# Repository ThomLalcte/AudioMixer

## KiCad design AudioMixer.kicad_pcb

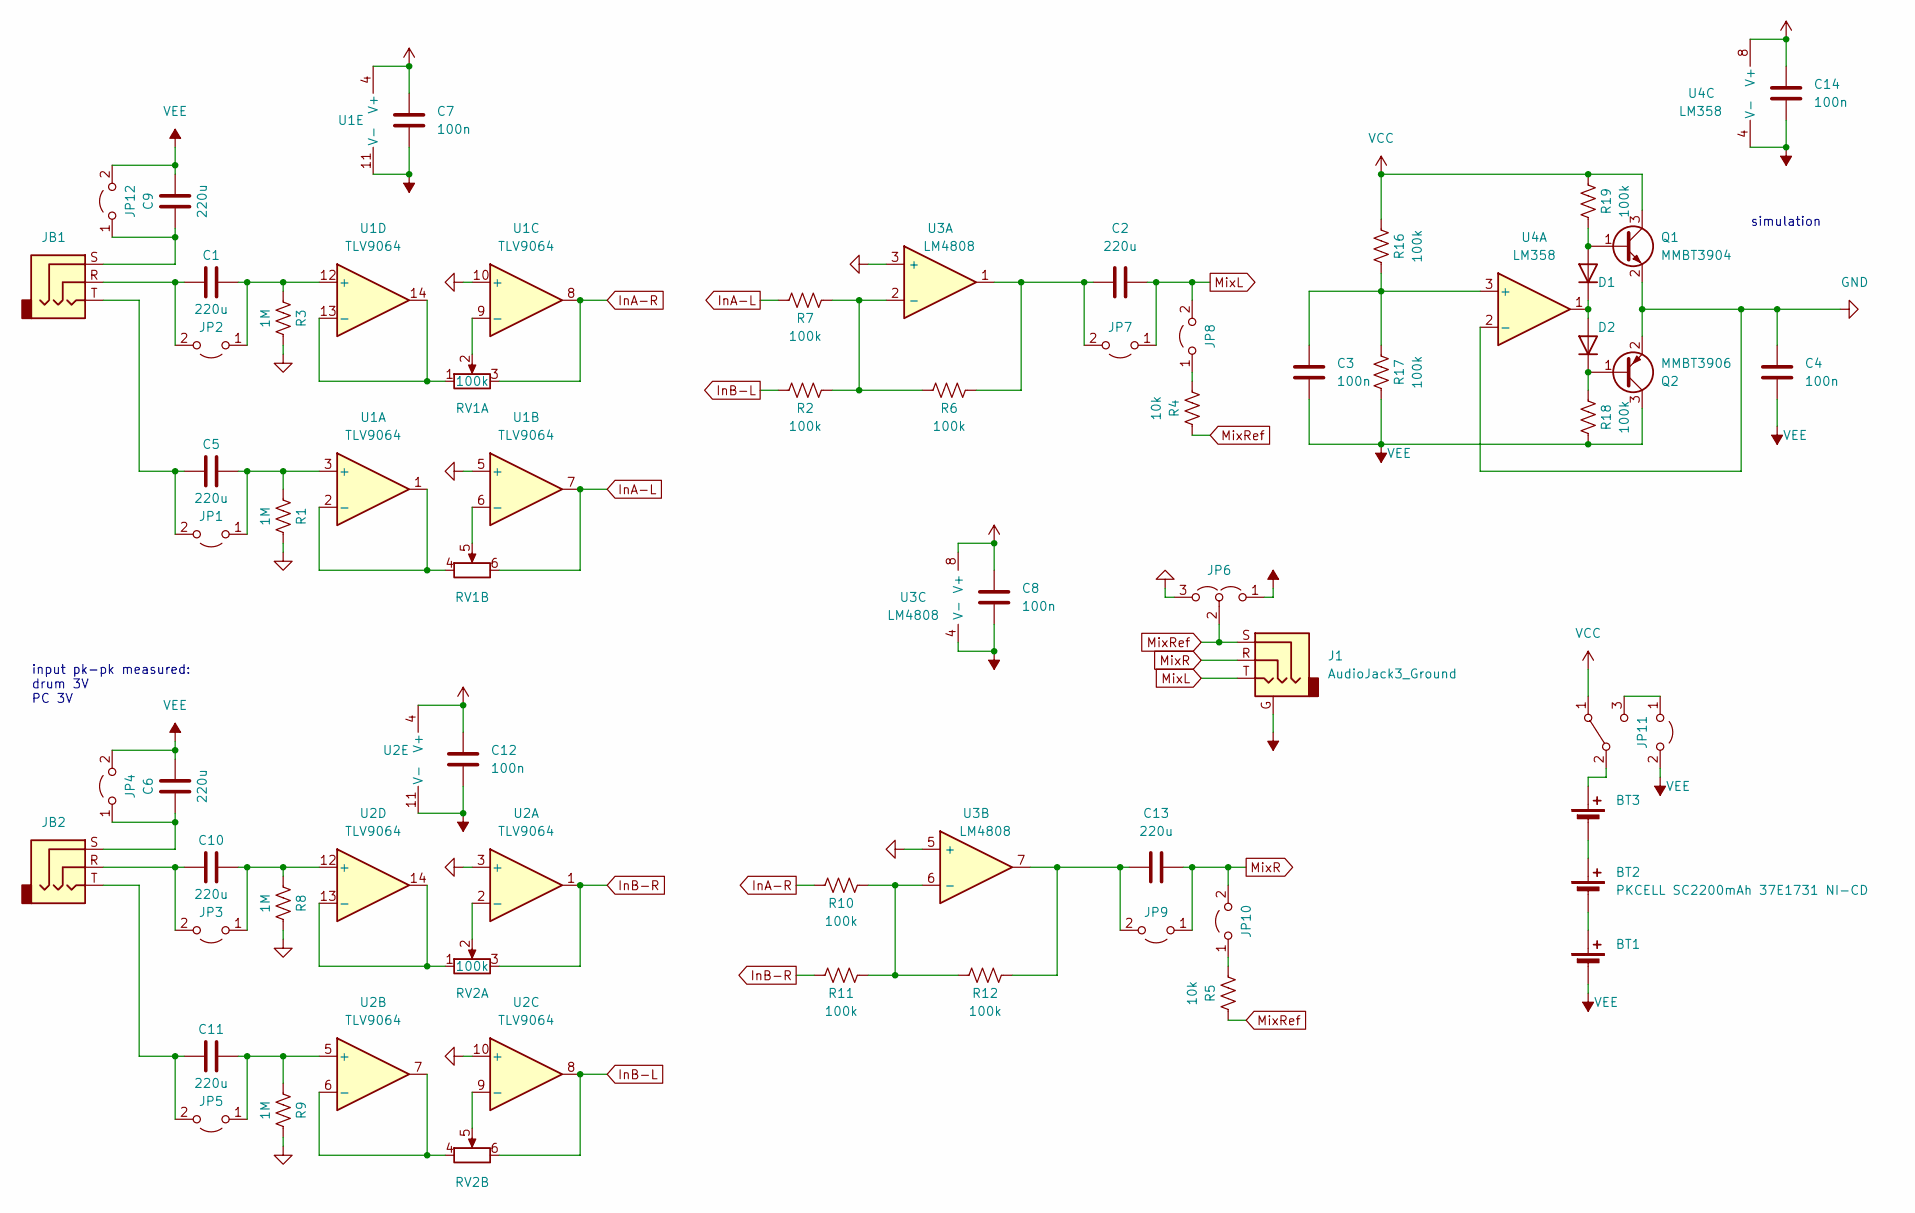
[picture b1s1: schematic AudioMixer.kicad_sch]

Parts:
BT1, BT2, BT3: PKCELL SC2200mAh 37E1731 NI-CD; Ni-Cd
C1, C2, C5, C6, C9, C10, C11, C13: 220u; CP_Radial_D5.0mm_P2.00mm
C3, C4, C7, C8, C12, C14: 100n; C_0603_1608Metric_Pad1.08x0.95mm_HandSolder
D1, D2: 1N4148; D_SOD-123
J1: AudioJack3_Ground; Jack_3.5mm_CUI_SJ-3524-SMT_Horizontal
JB1, JB2: AudioJack3; C18594
JP1, JP2, JP3, JP4, JP5, JP7, JP8, JP9, JP10, JP11, JP12: Jumper_2_Open; PinHeader_1x02_P2.54mm_Vertical
JP6: Jumper_3_Open; PinHeader_1x03_P2.54mm_Vertical
Q1: MMBT3904; SOT-23
Q2: MMBT3906; SOT-23
R1, R3, R8, R9: 1M; R_0805_2012Metric_Pad1.20x1.40mm_HandSolder
R2, R6, R7, R10, R11, R12, R16, R17, R18, R19: 100k; R_0805_2012Metric_Pad1.20x1.40mm_HandSolder
R4, R5: 10k; R_0805_2012Metric_Pad1.20x1.40mm_HandSolder
RV1, RV2: 100k; Potentiometer_Bourns_PTA3044_Double_Slide
SW1: SW_SPDT; C128955
U1, U2: TLV9064; TSSOP-14_4.4x5mm_P0.65mm
U3: LM4808; SOIC-8_3.9x4.9mm_P1.27mm
U4: LM358; SOIC-8_3.9x4.9mm_P1.27mm

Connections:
GND: C4.1, JP6.3 (B), Q1.2 (E), Q2.2 (E), R1.1, R3.1, R8.1, R9.1, U1.5 (+), U1.10 (+), U2.3 (+), U2.10 (+), U3.3 (+), U3.5 (+), U4.2 (-)
InA-L: R7.1, RV1.6, U1.7
InA-R: R10.1, RV1.3, U1.8
InB-L: R2.1, RV2.6, U2.8
InB-R: R11.1, RV2.3, U2.1
MixL: C2.2, J1.T, JP7.1 (A), JP8.2 (B)
MixR: C13.2, J1.R, JP9.1 (A), JP10.2 (B)
MixRef: J1.S, JP6.2 (C), R4.2, R5.2
unnamed: BT1.1 (+), BT2.2 (-)
unnamed: BT2.1 (+), BT3.2 (-)
unnamed: BT3.1 (+), SW1.2 (B)
unnamed: D1.2 (A), Q1.1 (B), R19.1
unnamed: D1.1 (K), D2.2 (A), U4.1
unnamed: D2.1 (K), Q2.1 (B), R18.2
unnamed: C5.1, JP1.1 (A), R1.2, U1.3 (+)
unnamed: C5.2, JB1.T, JP1.2 (B)
unnamed: C1.1, JP2.1 (A), R3.2, U1.12 (+)
unnamed: C1.2, JB1.R, JP2.2 (B)
unnamed: C10.1, JP3.1 (A), R8.2, U2.12 (+)
unnamed: C10.2, JB2.R, JP3.2 (B)
unnamed: C6.2, JB2.S, JP4.1 (A)
unnamed: C11.1, JP5.1 (A), R9.2, U2.5 (+)
unnamed: C11.2, JB2.T, JP5.2 (B)
unnamed: C2.1, JP7.2 (B), R6.2, U3.1
unnamed: JP8.1 (A), R4.1
unnamed: C13.1, JP9.2 (B), R12.2, U3.7
unnamed: JP10.1 (A), R5.1
unnamed: JP11.1 (A), SW1.3 (C)
unnamed: C9.2, JB1.S, JP12.1 (A)
unnamed: RV1.4, U1.1, U1.2 (-)
unnamed: RV1.5, U1.6 (-)
unnamed: RV1.2, U1.9 (-)
unnamed: RV1.1, U1.13 (-), U1.14
unnamed: RV2.2, U2.2 (-)
unnamed: RV2.4, U2.6 (-), U2.7
unnamed: RV2.5, U2.9 (-)
unnamed: RV2.1, U2.13 (-), U2.14
unnamed: R2.2, R6.1, R7.2, U3.2 (-)
unnamed: R10.2, R11.2, R12.1, U3.6 (-)
unnamed: C3.1, R16.1, R17.2, U4.3 (+)
VCC: C7.2, C8.2, C12.2, C14.2, Q1.3 (C), R16.2, R19.2, SW1.1 (A), U1.4 (V+), U2.4 (V+), U3.8 (V+), U4.8 (V+)
VEE: BT1.2 (-), C3.2, C4.2, C6.1, C7.1, C8.1, C9.1, C12.1, C14.1, J1.G, J1.TN, JP4.2 (B), JP6.1 (A), JP11.2 (B), JP12.2 (B), Q2.3 (C), R17.1, R18.1, U1.11 (V-), U2.11 (V-), U3.4 (V-), U4.4 (V-)

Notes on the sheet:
simulation
input pk-pk measured: drum 3V PC 3V

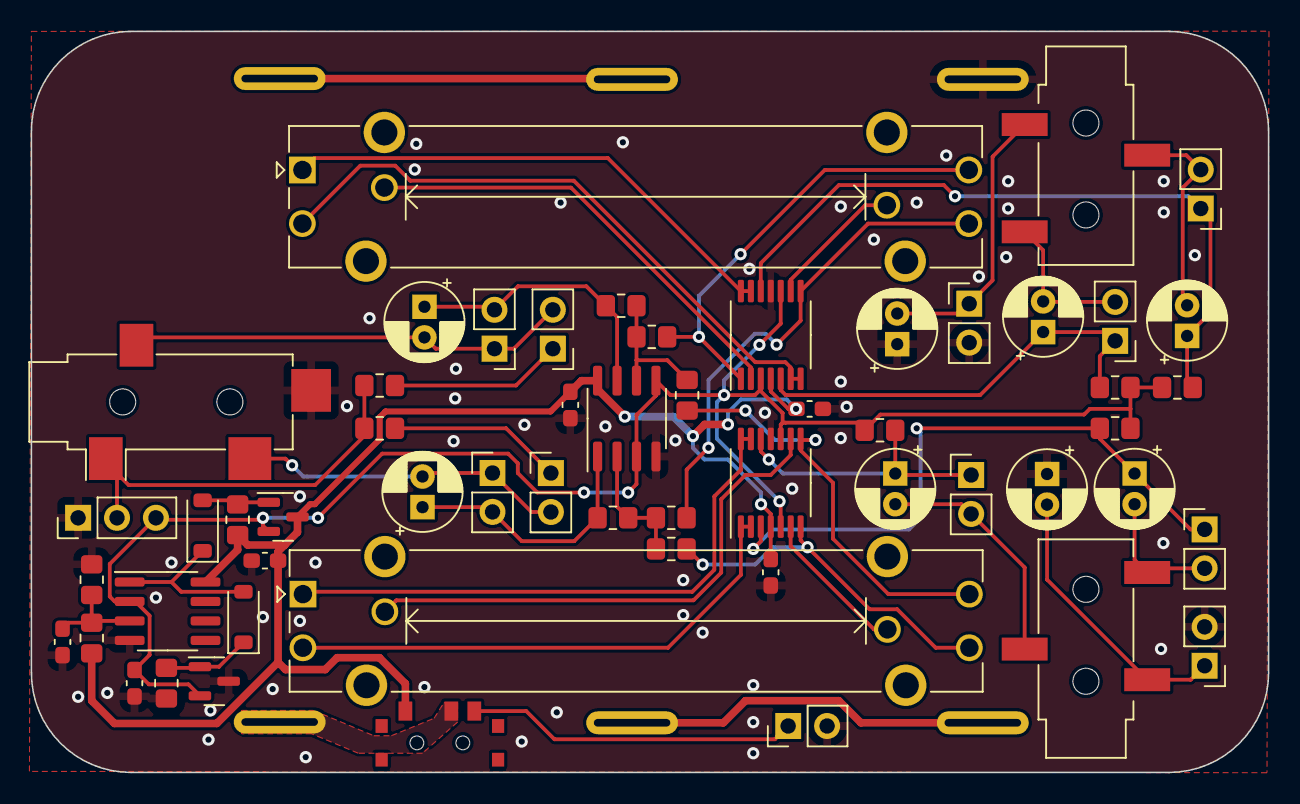
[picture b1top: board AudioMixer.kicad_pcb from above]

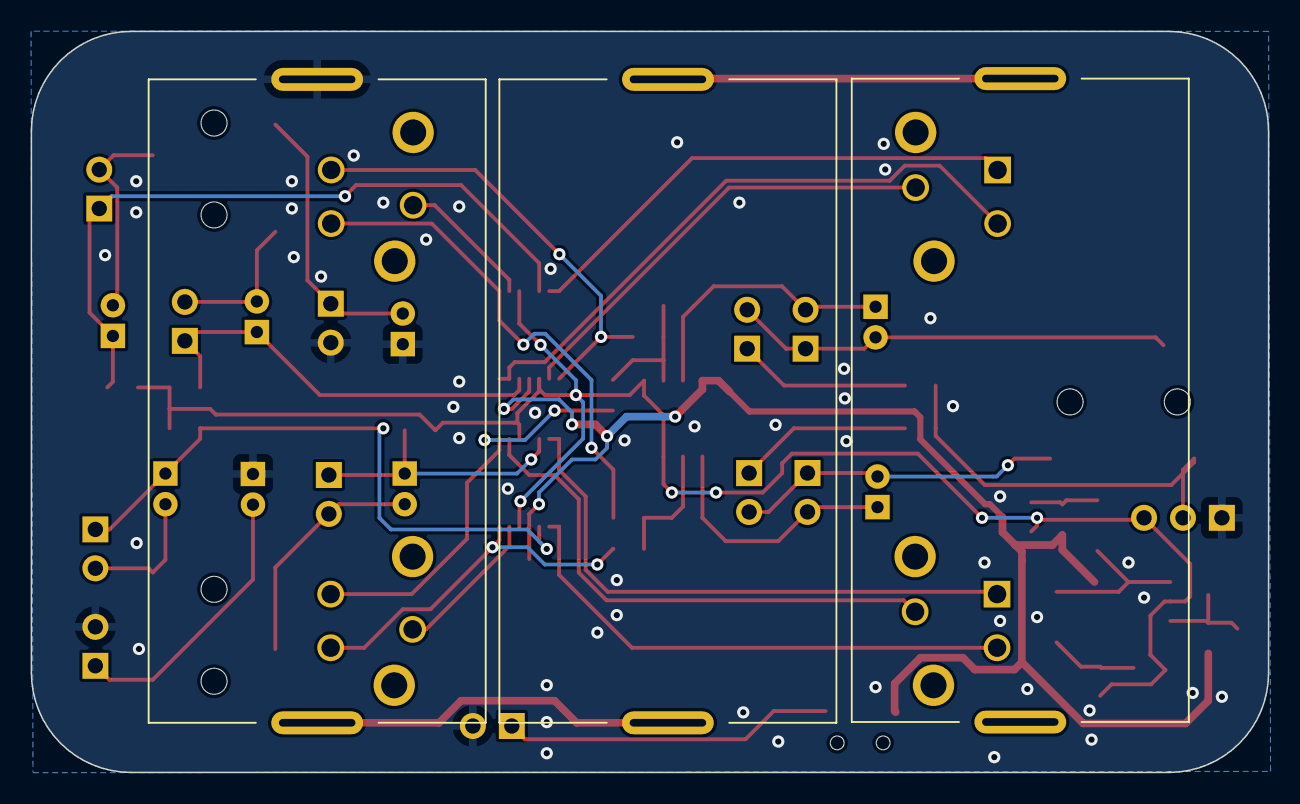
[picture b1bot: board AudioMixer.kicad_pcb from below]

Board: 2 copper layers, 80.8 x 48.4 mm, 59 parts (3 on the bottom side), 42 nets.

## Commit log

2024-01-16 init
